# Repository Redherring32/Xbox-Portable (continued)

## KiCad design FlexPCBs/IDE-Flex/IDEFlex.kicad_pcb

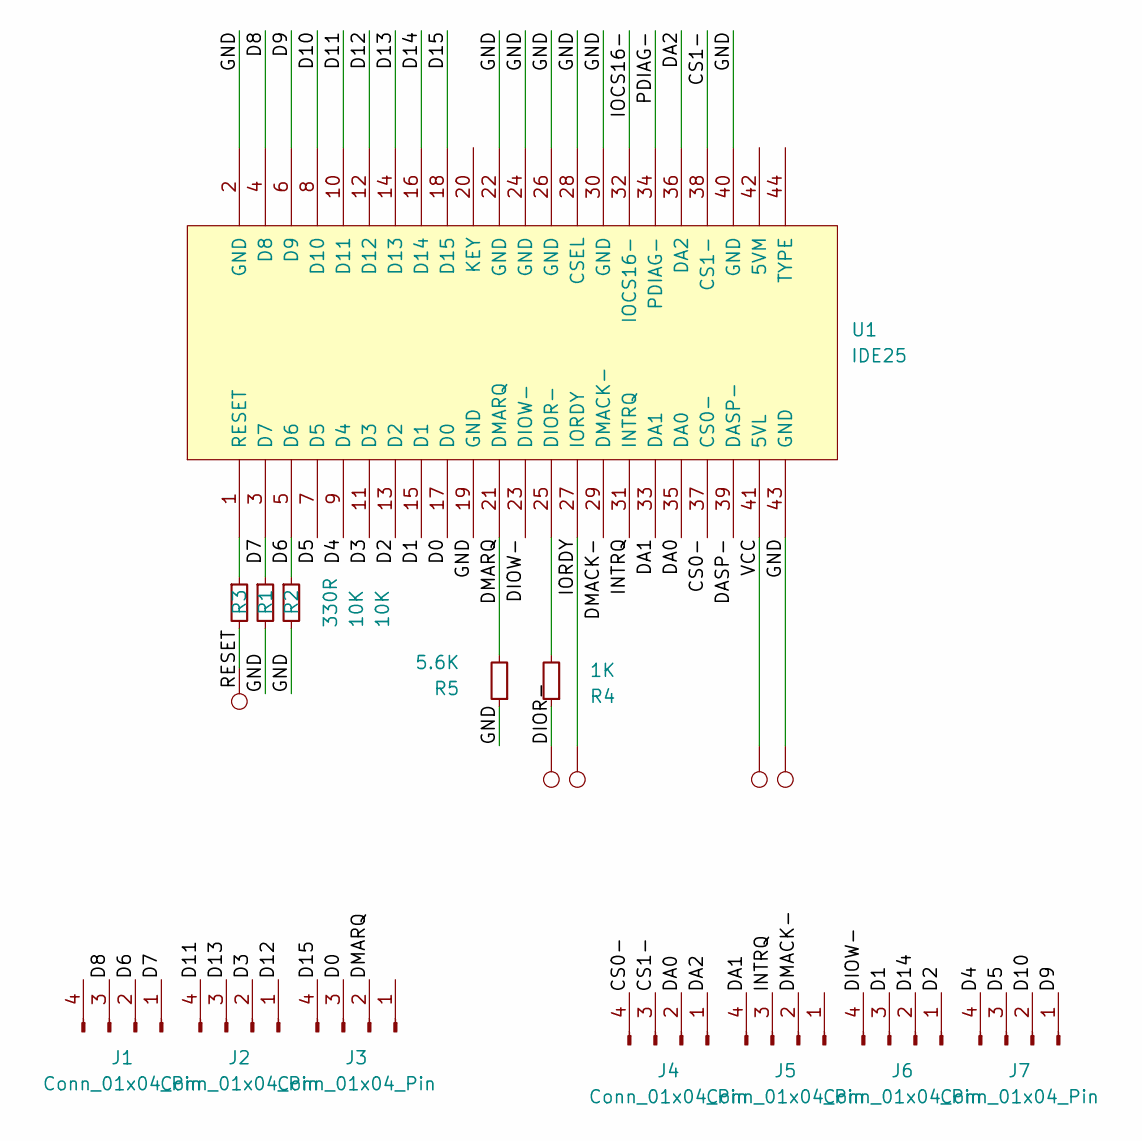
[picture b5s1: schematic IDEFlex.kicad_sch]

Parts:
J1, J2, J3, J4, J5, J6, J7: Conn_01x04_Pin; EdgePad
R1, R2: 10K; R_0402_1005Metric
R3: 330R; R_0402_1005Metric
R4: 1K; R_0402_1005Metric
R5: 5.6K; R_0402_1005Metric
TP1, TP2, TP3, TP4, TP5: TestPoint; TestPoint_Pad_D1.0mm
U1: IDE25; IDE

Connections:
/CS0-: J4.4, U1.37 (CS0-)
/CS1-: J4.3, U1.38 (CS1-)
/D0: J3.3, U1.17 (D0)
/D1: J6.3, U1.15 (D1)
/D2: J6.1, U1.13 (D2)
/D3: J2.2, U1.11 (D3)
/D4: J7.4, U1.9 (D4)
/D5: J7.3, U1.7 (D5)
/D6: J1.2, R2.1, U1.5 (D6)
/D7: J1.1, R1.1, U1.3 (D7)
/D8: J1.3, U1.4 (D8)
/D9: J7.1, U1.6 (D9)
/D10: J7.2, U1.8 (D10)
/D11: J2.4, U1.10 (D11)
/D12: J2.1, U1.12 (D12)
/D13: J2.3, U1.14 (D13)
/D14: J6.2, U1.16 (D14)
/D15: J3.4, U1.18 (D15)
/DA0: J4.2, U1.35 (DA0)
/DA1: J5.4, U1.33 (DA1)
/DA2: J4.1, U1.36 (DA2)
/DASP-: U1.39 (DASP-)
/DIOR-: R4.1, TP5.1
/DIOW-: J6.4, U1.23 (DIOW-)
/DMACK-: J5.2, U1.29 (DMACK-)
/DMARQ: J3.2, R5.2, U1.21 (DMARQ)
/GND: R1.2, R2.2, R5.1, TP4.1, U1.2 (GND), U1.19 (GND), U1.22 (GND), U1.24 (GND), U1.26 (GND), U1.28 (CSEL), U1.30 (GND), U1.40 (GND), U1.43 (GND)
/INTRQ: J5.3, U1.31 (INTRQ)
/IOCS16-: U1.32 (IOCS16-)
/IORDY: TP2.1, U1.27 (IORDY)
/PDIAG-: U1.34 (PDIAG-)
/RESET: R3.2, TP1.1
/VCC: TP3.1, U1.41 (5VL)
unnamed: R4.2, U1.25 (DIOR-)
unnamed: R3.1, U1.1 (RESET)

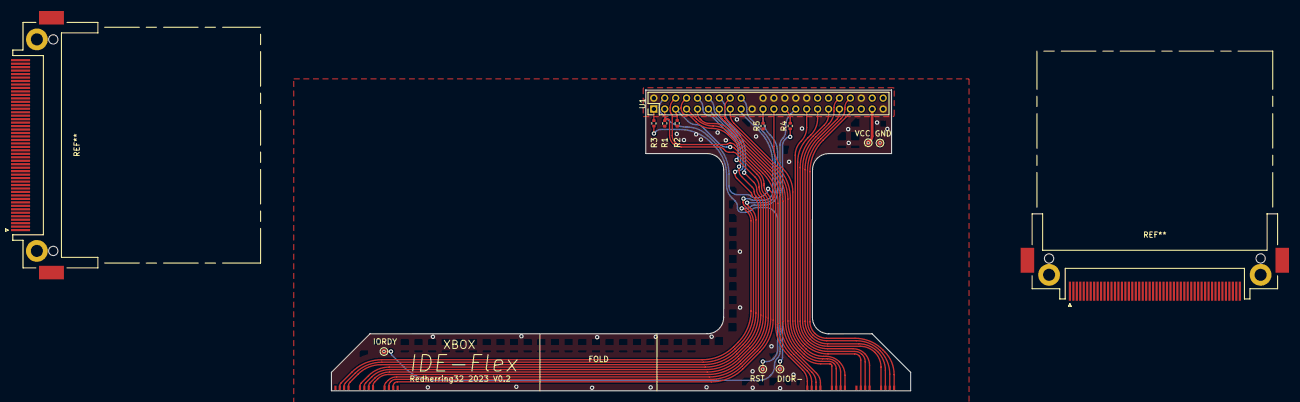
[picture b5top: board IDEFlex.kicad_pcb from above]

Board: 11 copper layers, 106.1 x 55.1 mm, 18 parts (0 on the bottom side), 32 nets.

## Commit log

2024-06-10 Add PSU files
2024-06-10 Update README.MD
    Add image
2024-06-10 Add temporary BOM.csv
2024-06-10 Create LICENSE
2024-06-10 Add files for flex PCBs and controller PCBs
